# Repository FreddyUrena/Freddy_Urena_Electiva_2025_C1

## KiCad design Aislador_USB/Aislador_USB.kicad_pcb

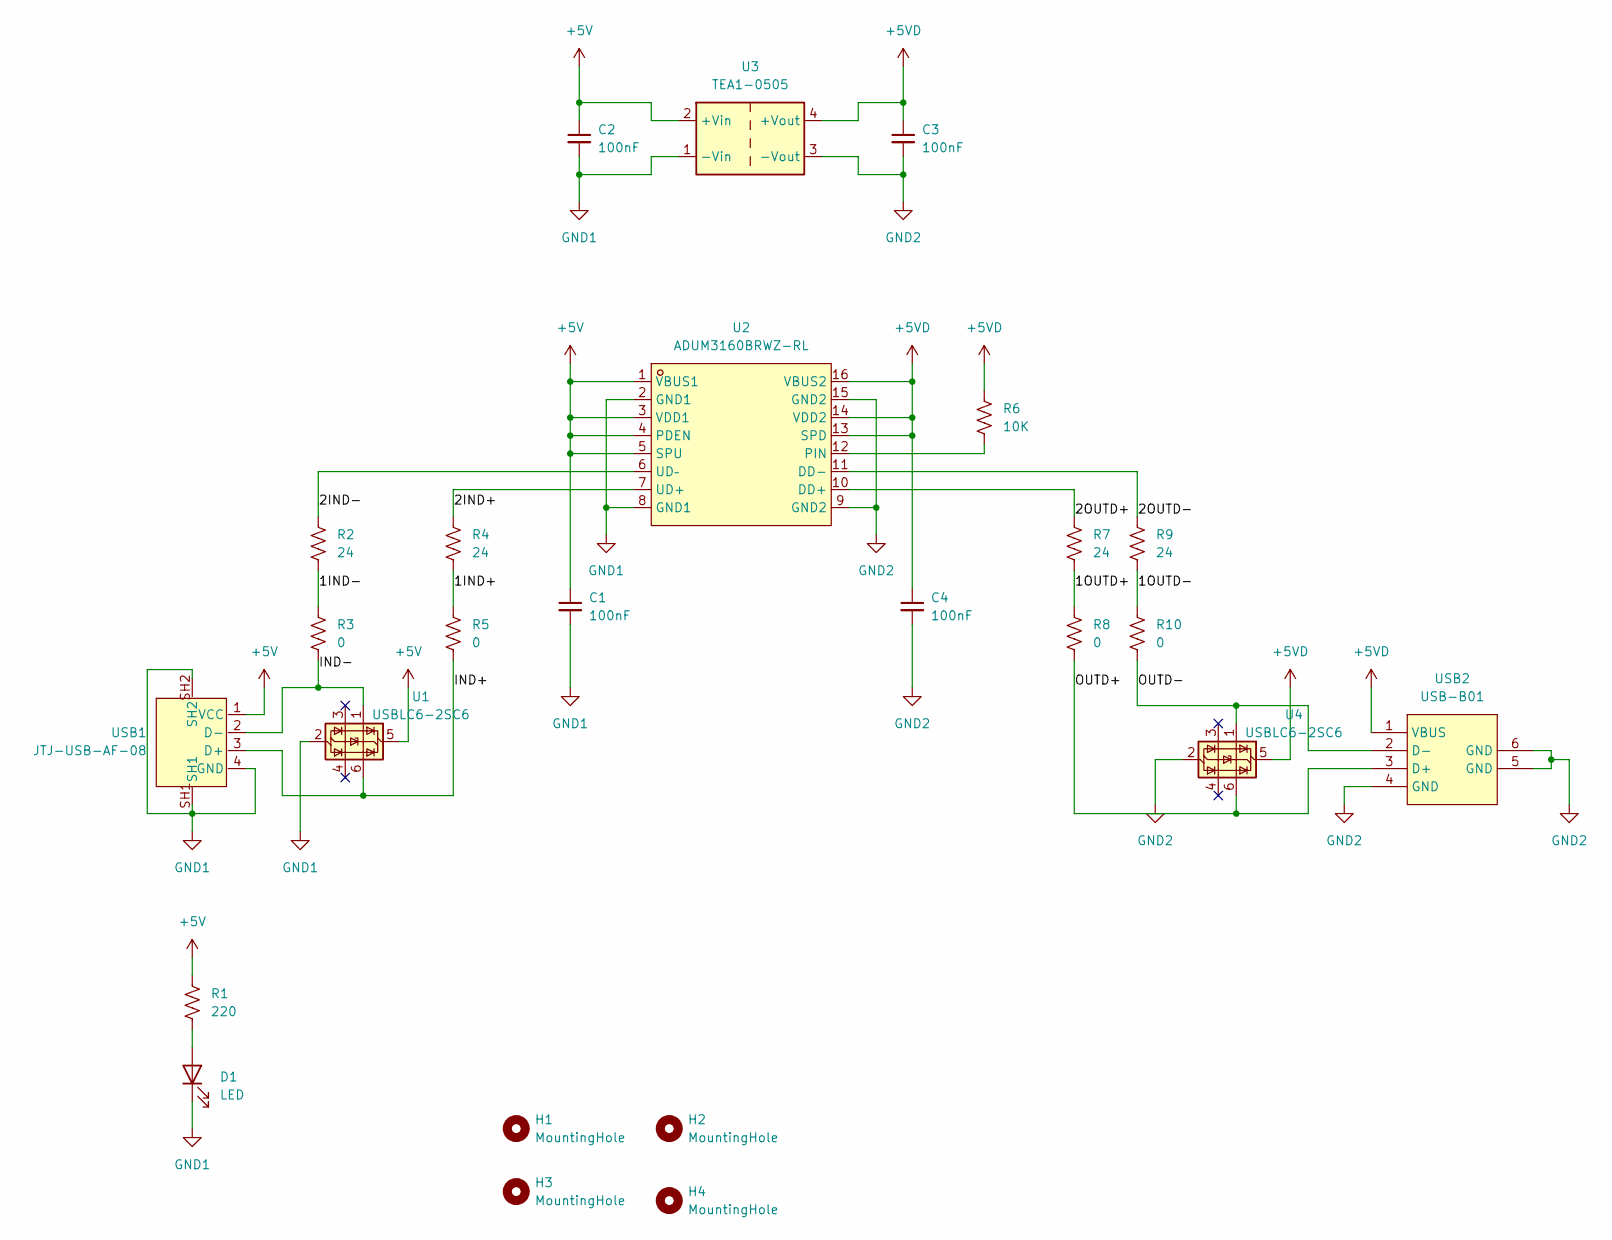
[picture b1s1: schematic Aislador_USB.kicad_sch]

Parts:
C1, C2, C3, C4: 100nF; C_0603_1608Metric
D1: LED; LED_0603_1608Metric
H1, H2, H3, H4: MountingHole; MountingHole_3.2mm_M3
R1: 220; R_0603_1608Metric
R2, R4, R7, R9: 24; R_0603_1608Metric
R3, R5, R8, R10: 0; R_0603_1608Metric
R6: 10K; R_0603_1608Metric
U1, U4: USBLC6-2SC6; SOT-23-6
U2: ADUM3160BRWZ-RL; SOIC-16_L10.3-W7.5-P1.27-LS10.3-BL; LCSC Part C284149
U3: TEA1-0505; Converter_DCDC_TRACO_TEA1-xxxx_THT
USB1: JTJ-USB-AF-08; USB-A-TH__USB-AF-90; LCSC Part C2345
USB2: USB-B01; USB-B-TH_USB-B01; LCSC Part C498173

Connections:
+5V: C1.1, C2.1, R1.1, U1.5 (VBUS), U2.1 (VBUS1), U2.3 (VDD1), U2.4 (PDEN), U2.5 (SPU), U3.2 (+Vin), USB1.1 (VCC)
+5VD: C3.1, C4.1, R6.1, U2.13 (SPD), U2.14 (VDD2), U2.16 (VBUS2), U3.4 (+Vout), U4.5 (VBUS), USB2.1 (VBUS)
/1IND+: R4.2, R5.1
/1IND-: R2.2, R3.1
/1OUTD+: R7.2, R8.1
/1OUTD-: R9.2, R10.1
/2IND+: R4.1, U2.7 (UD+)
/2IND-: R2.1, U2.6 (UD–)
/2OUTD+: R7.1, U2.10 (DD+)
/2OUTD-: R9.1, U2.11 (DD-)
/IND+: R5.2, U1.6 (I/O1), USB1.3 (D+)
/IND-: R3.2, U1.1 (I/O1), USB1.2 (D-)
/OUTD+: R8.2, U4.6 (I/O1), USB2.3 (D+)
/OUTD-: R10.2, U4.1 (I/O1), USB2.2 (D-)
GND1: C1.2, C2.2, D1.1 (K), U1.2 (GND), U2.2 (GND1), U2.8 (GND1), U3.1 (-Vin), USB1.4 (GND), USB1.SH1, USB1.SH2
GND2: C3.2, C4.2, U2.9 (GND2), U2.15 (GND2), U3.3 (-Vout), U4.2 (GND), USB2.4 (GND), USB2.5 (GND), USB2.6 (GND)
unnamed: D1.2 (A), R1.2
unnamed: R6.2, U2.12 (PIN)

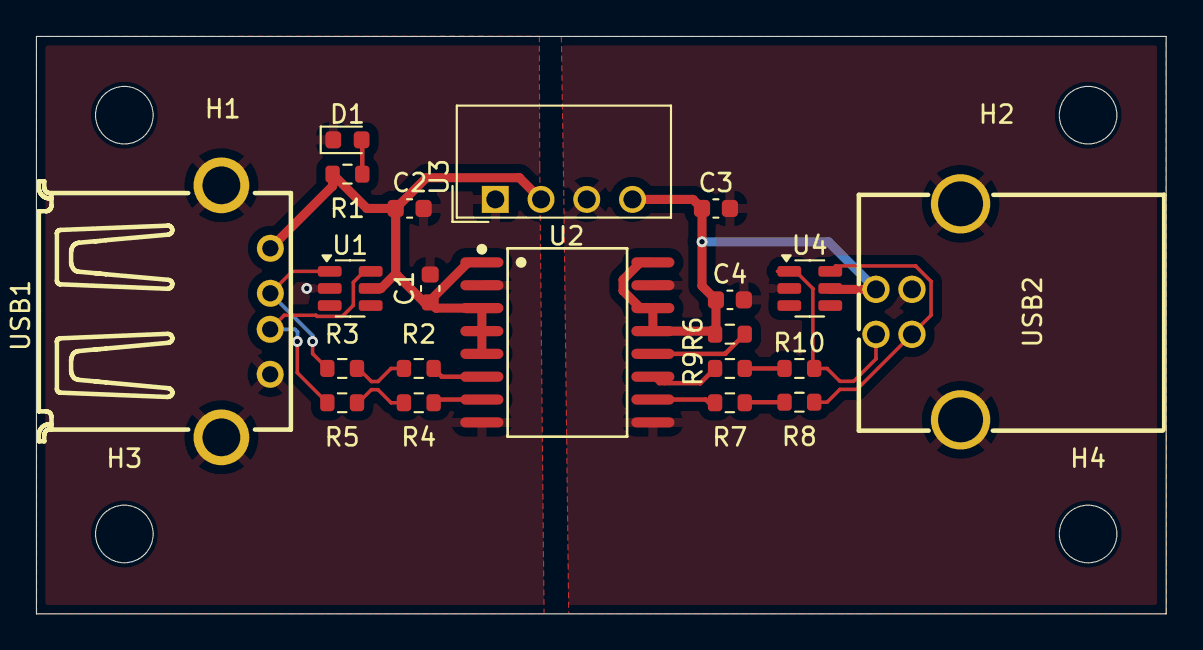
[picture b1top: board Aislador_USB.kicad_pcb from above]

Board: 2 copper layers, 62.8 x 32.1 mm, 25 parts (0 on the bottom side), 18 nets.

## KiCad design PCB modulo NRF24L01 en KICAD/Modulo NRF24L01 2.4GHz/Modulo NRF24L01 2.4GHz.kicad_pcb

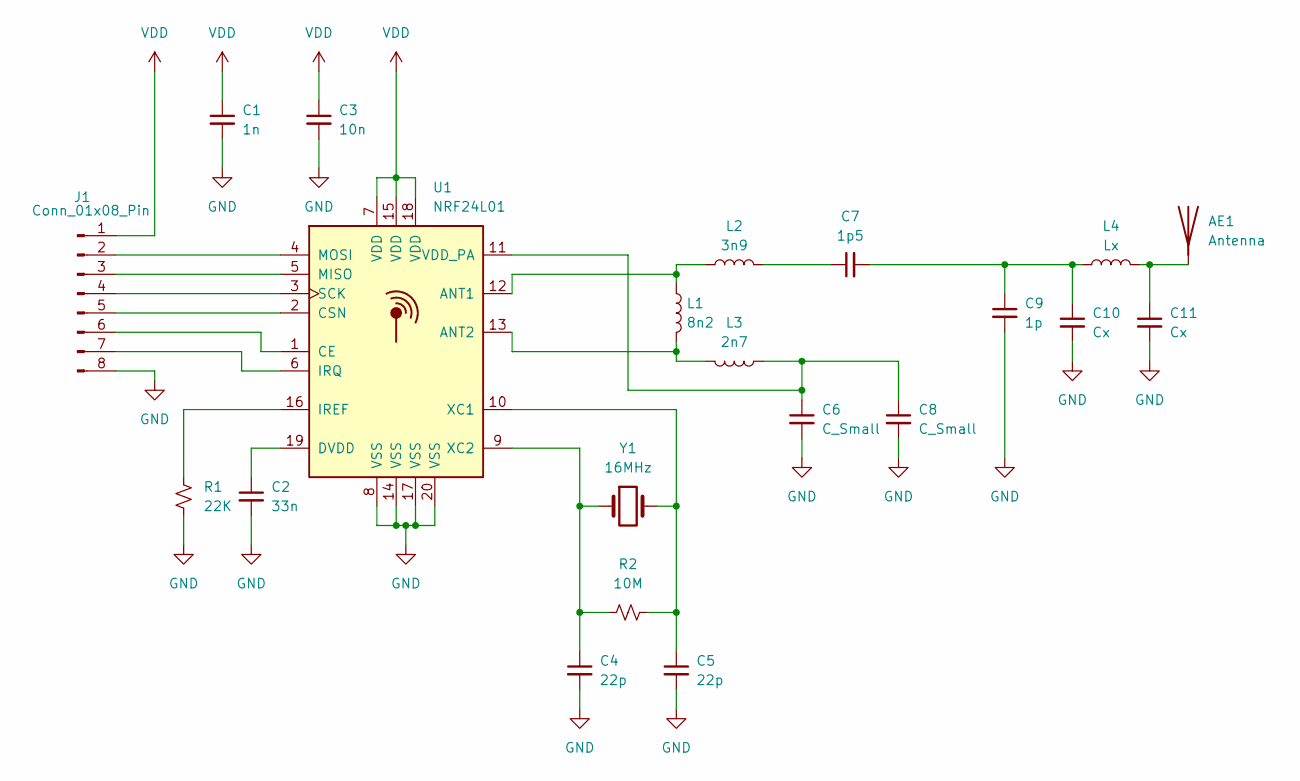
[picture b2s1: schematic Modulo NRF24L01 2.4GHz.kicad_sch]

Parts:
AE1: Antenna; Texas_SWRA117D_2.4GHz_Right
C1: 1n; C_0402_1005Metric
C2: 33n; C_0402_1005Metric
C3: 10n; C_0402_1005Metric
C4, C5: 22p; C_0402_1005Metric
C6, C8: C_Small; C_0402_1005Metric
C7: 1p5; C_0402_1005Metric
C9: 1p; C_0402_1005Metric
C10, C11: Cx; C_0402_1005Metric
J1: Conn_01x08_Pin; Hirose_DF13-08P-1.25DSA_1x08_P1.25mm_Vertical
L1: 8n2; L_0402_1005Metric
L2: 3n9; L_0402_1005Metric
L3: 2n7; L_0402_1005Metric
L4: Lx; L_0402_1005Metric
R1: 22K; R_0402_1005Metric
R2: 10M; R_0402_1005Metric
U1: NRF24L01; QFN-20-1EP_4x4mm_P0.5mm_EP2.5x2.5mm
Y1: 16MHz; Crystal_SMD_3215-2Pin_3.2x1.5mm

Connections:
GND: C1.2, C2.2, C3.2, C4.2, C5.2, C6.2, C8.2, C9.2, C10.2, C11.2, J1.8, R1.2, U1.8 (VSS), U1.14 (VSS), U1.17 (VSS), U1.20 (VSS)
unnamed: AE1.1 (A), C11.1, L4.2
unnamed: C7.1, L2.2
unnamed: C7.2, C9.1, C10.1, L4.1
unnamed: J1.2, U1.4 (MOSI)
unnamed: J1.3, U1.5 (MISO)
unnamed: J1.4, U1.3 (SCK)
unnamed: J1.5, U1.2 (CSN)
unnamed: J1.6, U1.1 (CE)
unnamed: J1.7, U1.6 (IRQ)
unnamed: L1.1, L2.1, U1.12 (ANT1)
unnamed: L1.2, L3.2, U1.13 (ANT2)
unnamed: C2.1, U1.19 (DVDD)
unnamed: R1.1, U1.16 (IREF)
unnamed: C6.1, C8.1, L3.1, U1.11 (VDD_PA)
unnamed: C5.1, R2.2, U1.10 (XC1), Y1.2
unnamed: C4.1, R2.1, U1.9 (XC2), Y1.1
VDD: C1.1, C3.1, J1.1, U1.7 (VDD), U1.15 (VDD), U1.18 (VDD)

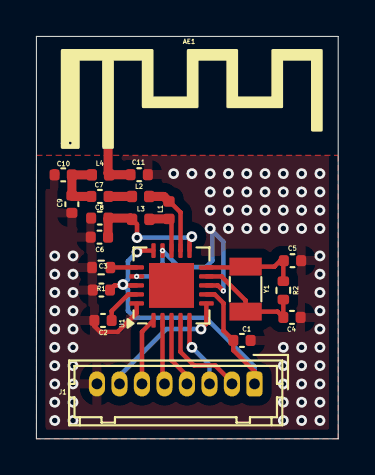
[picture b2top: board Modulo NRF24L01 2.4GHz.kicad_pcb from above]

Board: 2 copper layers, 16.8 x 22.4 mm, 21 parts (0 on the bottom side), 18 nets.

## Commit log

2025-02-12 primera tarea
2025-03-23 PCB_aislador_USB
2025-03-23 AisladorUSB
2025-04-25 250425
2025-04-25 200425
2025-04-25 250525
